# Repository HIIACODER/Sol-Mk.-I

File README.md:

# Sol Mk. I: A simple rocket flight controller
This project aims to create a flight controller for TVC, airbrakes, and fin control, that can charge and run off a 2 cell lipo battery and connect to it using an XT-30 connector. It uses a BMP581 barometer and an 
My goal with this project was to learn how to route properly and effectively on a PCB including how to manage decoupling caps and general power routing because that is what I struggle with. I also wanted a flight computer to use for my projects and test + learn C on.
I spent above 70 hours making this, and even more uncounted hours of research and thought, so I welcome any feedback.

This project should:
- help me develop a base to apply to future projects
- be a flight controller that I can reliably put in rockets

## PCB
Here is my PCB! This PCB was designed in KiCAD.

### General PCB design images

Schematic:

Top View (3d render):

Bottom View (3d render):

PCB Design:

First Layer: 

Second Layer:

Third Layer: 

Fourth Layer: 

Fifth Layer:

Sixth Layer:

### Layer Stackup
The board contains 6 layers. The purpose of all layers listed below.

| Layer | Description |
| :--- | :--- |
| 1 | Main routing layer |
| 2 | First ground layer for reference and signal separation |
| 3 | Second ground layer for reference and signal separation |
| 4 | Main Power Routing Layer |
| 5 | Third ground layer for reference and signal separation |
| 6 | Overflow routing layer |
### Flashing Instructions
Here are steps to flash a file to the MCU! 
1. Hold down the BOOTSEL button (the only button on the board) while plugging the board into your computer via USBC
2. The board will show up as a USB mass storage device
3. Compile your .uf2 binary file through external methods (C/C++ SDK, MicroPython, CircuitPython, etc)
4. Drag your compiled .uf2 file onto the drive. The board should automatically reboot and run the newly uploaded firmware!

## BOM

All SMD parts utilize 0402 passives, with 2 0603 for the MCU power to minimize board surface area. JLCPCB / LCSC part numbers are included below for reference.

| Item | Component / Description | Qty | Designators | Footprint | JLCPCB Part # | Unit Price (USD) |
| :--- | :--- | :---: | :--- | :--- | :--- | :---: |
| 1 | 1uF Capacitor | 3 | `C1, C10, C14` | `C_0402` | `C29266` | $0.0049 |
| 2 | 10uF Capacitor | 12 | `C11, C12, C13, C16, C17, C18, C2, C4, C5, C7, C8, C9` | `C_0402` | `C315248` | $0.0269 |
| 3 | 100nF Capacitor | 17 | `C15, C19, C20, C22, C24, C28, C29, C30, C31, C32, C33, C34, C35, C36, C40, C41, C42` | `C_0402` | `C1525` | $0.0029 |
| 4 | 10nF Capacitor | 1 | `C21` | `C_0402` | `C15195` | $0.0037 |
| 5 | 2.2uF Capacitor | 1 | `C23` | `C_0402` | `C444845` | $0.0094 |
| 6 | 4.7uF Capacitor | 2 | `C25, C26` | `C_0603` | `C19666` | $0.0150 |
| 7 | 47nF Capacitor | 1 | `C3` | `C_0402` | `C307434` | $0.0077 |
| 8 | 4.7uF Capacitor | 2 | `C37, C6` | `C_0402` | `C23733` | $0.0113 |
| 9 | 15pF Capacitor | 2 | `C38, C39` | `C_0402` | `C106997` | $0.0013 |
| 10 | TF-01A MicroSD Card Socket | 1 | `CARD1` | `TF-SMD_TF-01A` | `C91145` | $0.1931 |
| 11 | XT30UPB-M Power Connector | 1 | `CN1` | `CONN-TH_XT30UPB-M` | `C428721` | $0.2635 |
| 12 | USBLC6-2SC6 USB Protection IC | 1 | `D1` | `SOT-23-6_L2.9-W1.6-P0.95-LS2.8-BL` | `C7519` | $0.1559 |
| 13 | LED | 1 | `D2` | `LED0603-RD` | `C19273150` | $0.0114 |
| 14 | Green Signal LED | 1 | `D4` | `LED0603-GREEN` | `C22371297` | $0.0147 |
| 15 | 3-Pin Male Header | 5 | `H5, H6, H7, H8, H9` | `HDR-TH_3P-P2.54mm` | `C2937625` | $0.0200 |
| 16 | 1uH Inductor | 1 | `L1` | `APH252012C3R3MP01` | `C42455356` | $0.0365 |
| 17 | 3.3uH Inductor | 1 | `L2` | `B201610S3R3-101-T` | `C42411119` | $0.3377 |
| 18 | 5.1kΩ Resistor | 2 | `R1, R2` | `R0402` | `C25905` | $0.0014 |
| 19 | 10kΩ Resistor | 12 | `R6, R8, R9, R10, R11, R18, R19, R20, R21, R22, R23, R24` | `R0402` | `C25744` | $0.0010 |
| 20 | 10kΩ Thermistor | 1 | `TH1` | `R0402` | `C25744` | $0.0010 |
| 21 | 75kΩ Resistor | 1 | `R12` | `R0402` | `C2909383` | $0.0011 |
| 22 | 24kΩ Resistor | 1 | `R13` | `R0402` | `C25769` | $0.0012 |
| 23 | 100kΩ Resistor | 2 | `R14, R15` | `R0402` | `C25741` | $0.0011 |
| 24 | 105kΩ Resistor | 1 | `R16` | `R0402` | `C25742` | $0.0021 |
| 25 | 20kΩ Resistor | 1 | `R17` | `R0402` | `C25765` | $0.0011 |
| 26 | 1kΩ Resistor | 3 | `R7, R25, R26` | `R0402` | `C11702` | $0.0013 |
| 27 | 33Ω Resistor | 1 | `R27` | `R0402` | `C25105` | $0.0011 |
| 28 | 27Ω Resistor | 2 | `R28, R29` | `R0402` | `C2909343` | $0.0012 |
| 29 | 5.23kΩ Resistor | 1 | `R3` | `R0402` | `C2933105` | $0.0013 |
| 30 | 130Ω Resistor | 1 | `R30` | `R0402` | `C477610` | $0.0038 |
| 31 | 30.1kΩ Resistor | 1 | `R4` | `R0402` | `C29402` | $0.0012 |
| 32 | 383Ω Resistor | 1 | `R5` | `R0402` | `C49653730` | $0.0008 |
| 33 | TS-1088 Tactile Switch | 1 | `SW1` | `SW-SMD_L3.9-W3.0-P4.45` | `C720477` | $0.0516 |
| 34 | BQ25883RGER Battery Charger IC | 1 | `U1` | `VFQFPN-24_L4.0-W4.0-P0.50-BL-EP2.8` | `C544362` | $4.2249 |
| 35 | RP2354A Microcontroller | 1 | `U2` | `QFN-60_L7.0-W7.0-P0.40` | `C41378174` | $1.2562 |
| 36 | TPS82130SILR 3.3V Buck Converter | 2 | `U3, U4` | `USIP-8_L3.0-W2.8-P0.65` | `C473914` | $3.3384 |
| 37 | BMP581 Barometric Pressure Sensor | 1 | `U5` | `LGA-10_L2.0-W2.0-P0.50` | `C5362283` | $2.2539 |
| 38 | ICM-42688-P IMU Sensor | 1 | `U6` | `LGA-14_L3.0-W2.5-P0.50` | `C1850418` | $20.8264 |
| 39 | 12MHz Crystal | 1 | `U7` | `CRYSTAL-SMD_4P-L3.2-W2.5` | `C20625731` | $0.3817 |
| 40 | USB-C 16-Pin Connector | 1 | `USB1` | `USB-C-SMD_TYPE-C-16PIN-2MD-073` | `C2765186` | $0.0728 |

### Prices on JLCPCB:
NOTE: THESE PRICES DO NOT CONTAIN TAXES, AND ARE PRONE TO CHANGES
Parts Price (for 2): $96.3767

PCB (5x): $2.0 (if done without PCBA)

PCB (5x): $32.00

PCBA (2x): $194.03

Shipping on Global Standard Direct Line: $12.62

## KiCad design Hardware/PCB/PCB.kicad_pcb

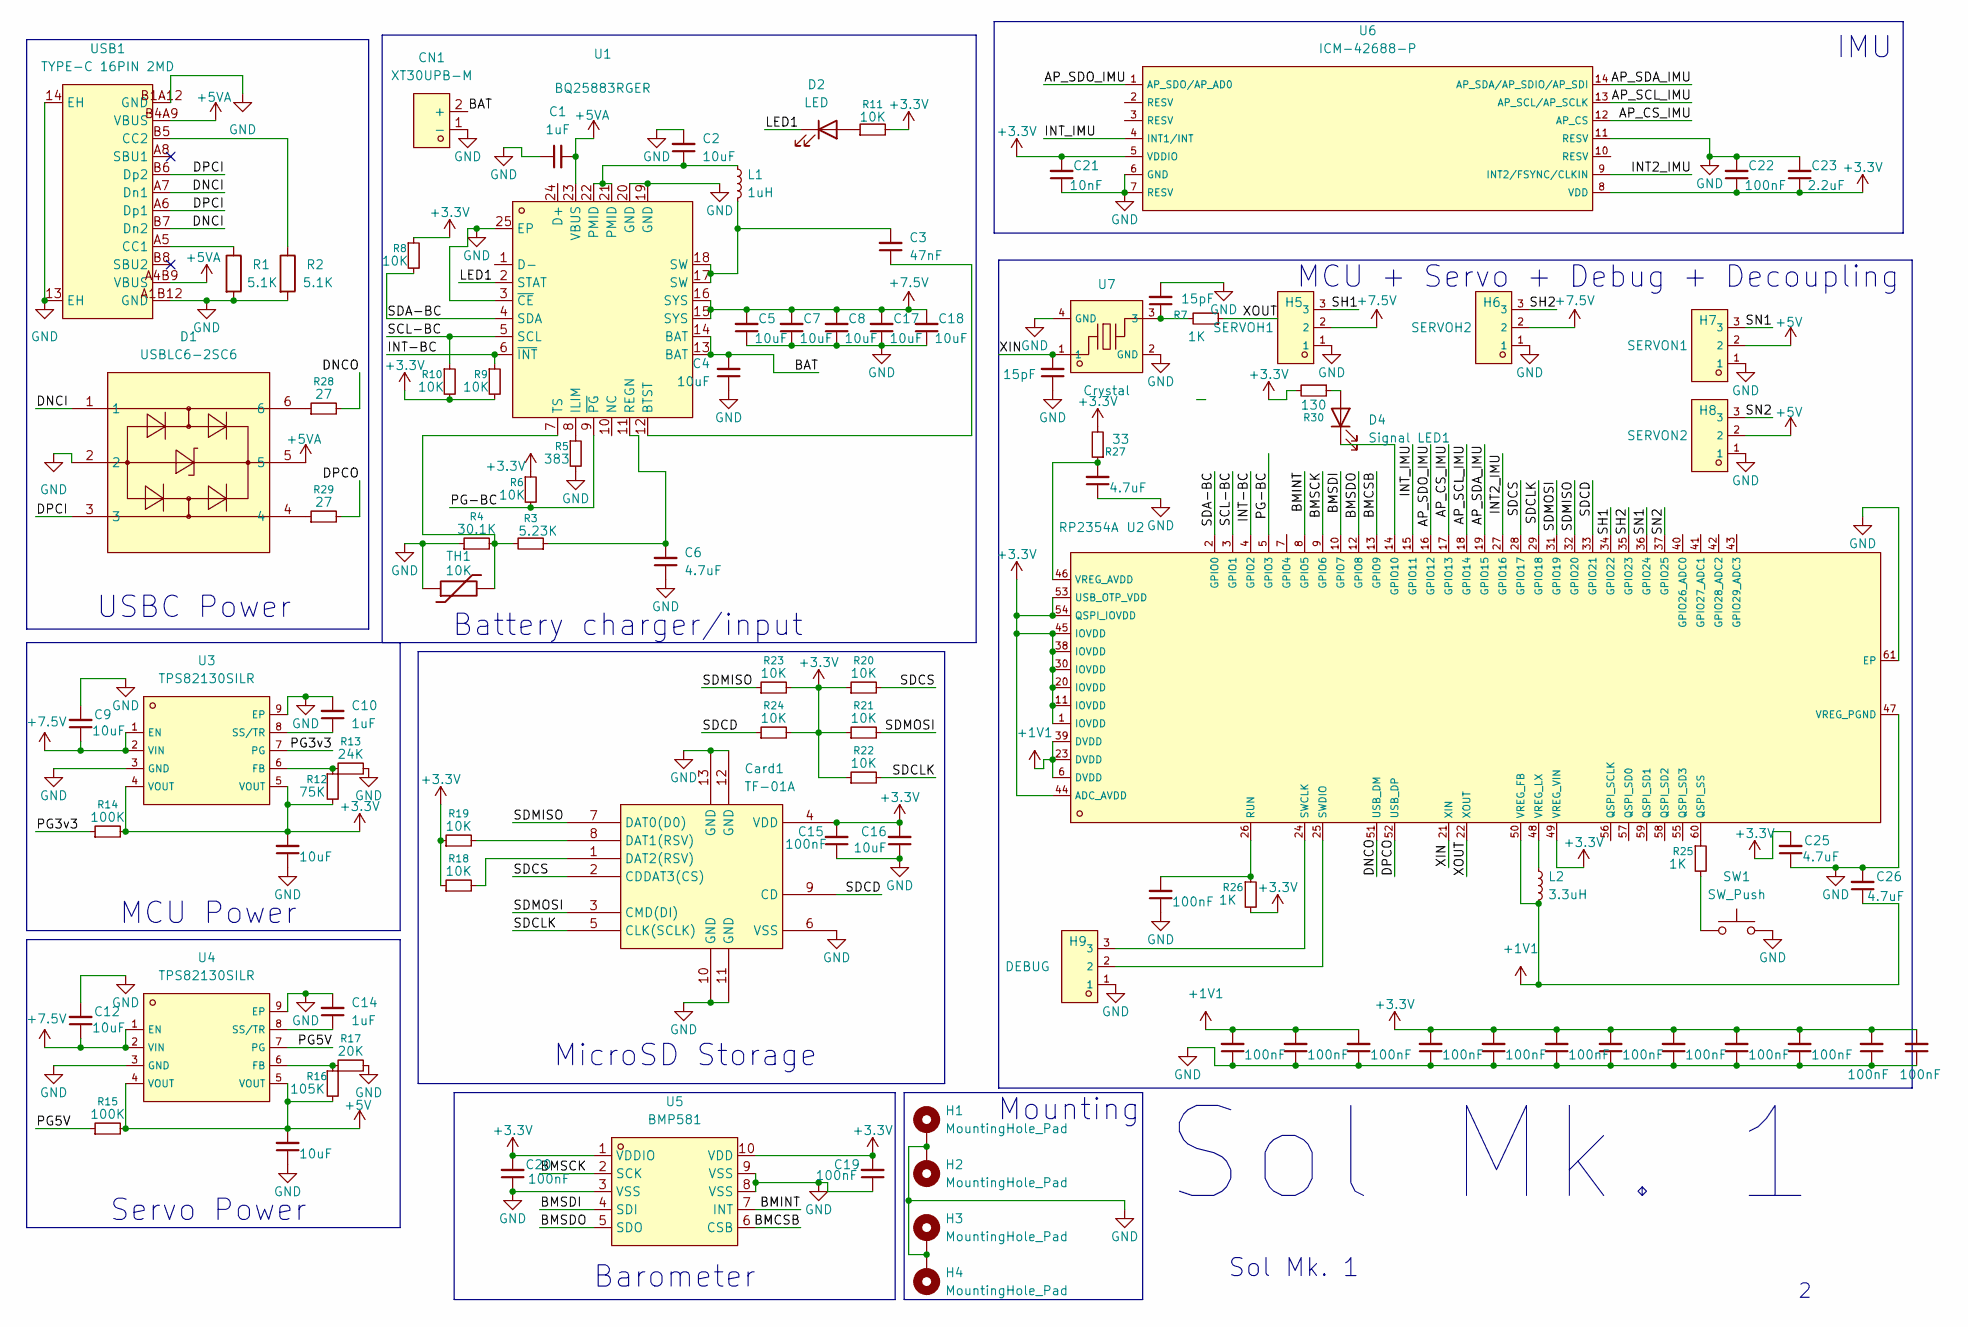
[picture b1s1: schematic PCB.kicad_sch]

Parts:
C1, C10, C14: 1uF; C_0402
C2, C4, C5, C7, C8, C9, C11, C12, C13, C16, C17, C18: 10uF; C_0402
C3: 47nF; C_0402
C6, C37: 4.7uF; C_0402
C15, C19, C20, C22, C24, C28, C29, C30, C31, C32, C33, C34, C35, C36, C40, C41, C42: 100nF; C_0402
C21: 10nF; C_0402
C23: 2.2uF; C_0402
C25, C26: 4.7uF; C_0603
C38, C39: 15pF; C_0402
CN1: XT30UPB-M; CONN-TH_XT30UPB-M; MPN XT30UPB-M; LCSC Part C428721
Card1: TF-01A; TF-SMD_TF-01A; MPN TF-01A; LCSC Part C91145
D1: USBLC6-2SC6; SOT-23-6_L2.9-W1.6-P0.95-LS2.8-BL; MPN USBLC6-2SC6; LCSC Part C7519
D2: LED; C19273150_LED0603-RD
D4: Signal LED1; C22371297_LED0603-RD_GREEN
H1, H2, H3, H4: MountingHole_Pad; MountingHole_2.5mm
H5: SERVOH1; C2937625_HDR-TH_3P-P2_54-V-M_PZ254V-11-03P; LCSC C2937625
H6: SERVOH2; C2937625_HDR-TH_3P-P2_54-V-M_PZ254V-11-03P; LCSC C2937625
H7: SERVON1; C2937625_HDR-TH_3P-P2_54-V-M_PZ254V-11-03P; LCSC C2937625
H8: SERVON2; C2937625_HDR-TH_3P-P2_54-V-M_PZ254V-11-03P; LCSC C2937625
H9: DEBUG; C2937625_HDR-TH_3P-P2_54-V-M_PZ254V-11-03P; LCSC C2937625
L1: 1uH; C42455356_IND-SMD_APH252012C3R3MP01
L2: 3.3uH; C42411119_IND-SMD_L2_0-W1_6_AOTA-B201610S3R3-101-T
R1, R2: 5.1K; R0402
R3: 5.23K; R0402
R4: 30.1K; R0402
R5: 383; R0402
R6, R8, R9, R10, R11, R18, R19, R20, R21, R22, R23, R24: 10K; R0402
R7, R25, R26: 1K; R0402
R12: 75K; R0402
R13: 24K; R0402
R14, R15: 100K; R0402
R16: 105K; R0402
R17: 20K; R0402
R27: 33; R0402
R28, R29: 27; R0402
R30: 130; R0402
SW1: SW_Push; C720477_SW-SMD_L3_9-W3_0-P4_45
TH1: 10K; R0402
U1: BQ25883RGER; VFQFPN-24_L4.0-W4.0-P0.50-BL-EP2.8; MPN BQ25883RGER; LCSC Part C544362
U2: RP2354A; C41378174_QFN-60_L7_0-W7_0-P0_40-TL-EP3_4; LCSC C41378174
U3, U4: TPS82130SILR; C473914_USIP-8_L3_0-W2_8-P0_65-TL-EP; LCSC C473914
U5: BMP581; LGA-10_L2.0-W2.0-P0.50-TL_BMP581; MPN BMP581; LCSC Part C5362283
U6: ICM-42688-P; C1850418_LGA-14_L3_0-W2_5-P0_50-TL; LCSC C1850418
U7: Crystal; C20625731_CRYSTAL-SMD_4P-L3_2-W2_5-BL; LCSC C20625731
USB1: TYPE-C 16PIN 2MD; USB-C-SMD_TYPE-C-16PIN-2MD-073; MPN TYPE-C 16PIN 2MD(073); LCSC Part C2765186

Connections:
+1V1: C26.1, C28.2, C29.2, C41.2, L2.2, U2.6 (DVDD), U2.23 (DVDD), U2.39 (DVDD), U2.50 (VREG_FB)
+3.3V: C11.2, C15.2, C16.2, C19.2, C20.2, C21.2, C22.1, C23.1, C25.2, C30.2, C31.2, C32.2, C33.2, C34.2, C35.2, C36.2, C40.2, C42.2, Card1.4 (VDD), R6.1, R8.1, R9.2, R10.2, R11.2, R12.2, R14.2, R18.1, R19.1, R20.1, R21.1, R22.1, R23.2, R24.2, R26.2, R27.2, R30.2, U2.1 (IOVDD), U2.11 (IOVDD), U2.20 (IOVDD), U2.30 (IOVDD), U2.38 (IOVDD), U2.44 (ADC_AVDD), U2.45 (IOVDD), U2.49 (VREG_VIN), U2.53 (USB_OTP_VDD), U2.54 (QSPI_IOVDD), U3.4 (VOUT), U3.5 (VOUT), U5.1 (VDDIO), U5.10 (VDD), U6.5 (VDDIO), U6.8 (VDD)
+5V: C13.2, H7.2, H8.2, R15.2, R16.2, U4.4 (VOUT), U4.5 (VOUT)
+5VA: C1.2, D1.5, U1.23 (VBUS), USB1.A4B9 (VBUS), USB1.B4A9 (VBUS)
+7.5V: C5.2, C7.2, C8.2, C9.1, C12.1, C17.2, C18.2, H5.2, H6.2, U1.15 (SYS), U1.16 (SYS), U3.1 (EN), U3.2 (VIN), U4.1 (EN), U4.2 (VIN)
/AP_CS_IMU: U2.17 (GPIO13), U6.12 (AP_CS)
/AP_SCL_IMU: U2.18 (GPIO14), U6.13 (AP_SCL/AP_SCLK)
/AP_SDA_IMU: U2.19 (GPIO15), U6.14 (AP_SDA/AP_SDIO/AP_SDI)
/AP_SDO_IMU: U2.16 (GPIO12), U6.1 (AP_SDO/AP_AD0)
/BAT: C4.2, CN1.2 (+), U1.13 (BAT), U1.14 (BAT)
/BMCSB: U2.13 (GPIO9), U5.6 (CSB)
/BMINT: U2.8 (GPIO5), U5.7 (INT)
/BMSCK: U2.9 (GPIO6), U5.2 (SCK)
/BMSDI: U2.10 (GPIO7), U5.4 (SDI)
/BMSDO: U2.12 (GPIO8), U5.5 (SDO)
/DNCI: D1.1, USB1.A7 (Dn1), USB1.B7 (Dn2)
/DNCO: R28.2, U2.51 (USB_DM)
/DPCI: D1.3, USB1.A6 (Dp1), USB1.B6 (Dp2)
/DPCO: R29.2, U2.52 (USB_DP)
/INT2_IMU: U2.27 (GPIO16), U6.9 (INT2/FSYNC/CLKIN)
/INT-BC: R9.1, U1.6 (~INT), U2.4 (GPIO2)
/INT_IMU: U2.15 (GPIO11), U6.4 (INT1/INT)
/LED1: D2.1 (K), U1.2 (STAT)
/PG3v3: R14.1, U3.7 (PG)
/PG5V: R15.1, U4.7 (PG)
/PG-BC: R6.2, U1.9 (~PG), U2.5 (GPIO3)
/SCL-BC: R10.1, U1.5 (SCL), U2.3 (GPIO1)
/SDA-BC: R8.2, U1.4 (SDA), U2.2 (GPIO0)
/SDCD: Card1.9 (CD), R24.1, U2.33 (GPIO21)
/SDCLK: Card1.5 (CLK(SCLK)), R22.2, U2.29 (GPIO18)
/SDCS: Card1.2 (CDDAT3(CS)), R20.2, U2.28 (GPIO17)
/SDMISO: Card1.7 (DAT0(D0)), R23.1, U2.32 (GPIO20)
/SDMOSI: Card1.3 (CMD(DI)), R21.2, U2.31 (GPIO19)
/SH1: H5.3, U2.34 (GPIO22)
/SH2: H6.3, U2.35 (GPIO23)
/SN1: H7.3, U2.36 (GPIO24)
/SN2: H8.3, U2.37 (GPIO25)
/XIN: C38.2, U2.21 (XIN), U7.1
/XOUT: R7.1, U2.22 (XOUT)
GND: C1.1, C2.2, C4.1, C5.1, C6.1, C7.1, C8.1, C9.2, C10.2, C11.1, C12.2, C13.1, C14.2, C15.1, C16.1, C17.1, C18.1, C19.1, C20.1, C21.1, C22.2, C23.2, C24.1, C25.1, C26.2, C28.1, C29.1, C30.1, C31.1, C32.1, C33.1, C34.1, C35.1, C36.1, C37.1, C38.1, C39.2, C40.1, C41.1, C42.1, CN1.1 (-), Card1.6 (VSS), Card1.10 (GND), Card1.11 (GND), Card1.12 (GND), Card1.13 (GND), D1.2, H1.1, H2.1, H3.1, H4.1, H5.1, H6.1, H7.1, H8.1, H9.1, R1.2, R2.2, R4.1, R5.2, R13.2, R17.2, SW1.2, TH1.1, U1.3 (~CE), U1.19 (GND), U1.20 (GND), U1.25 (EP), U2.47 (VREG_PGND), U2.61 (EP), U3.3 (GND), U3.9 (EP), U4.3 (GND), U4.9 (EP), U5.3 (VSS), U5.8 (VSS), U5.9 (VSS), U6.6 (GND), U6.7 (RESV), U6.11 (RESV), U7.2 (GND), U7.4 (GND), USB1.13 (EH), USB1.14 (EH), USB1.A1B12 (GND), USB1.B1A12 (GND)
unnamed: C2.1, L1.1, U1.21 (PMID), U1.22 (PMID)
unnamed: C3.2, L1.2, U1.17 (SW), U1.18 (SW)
unnamed: C39.1, R7.2, U7.3
unnamed: Card1.8 (DAT1(RSV)), R19.2
unnamed: Card1.1 (DAT2(RSV)), R18.2
unnamed: D1.4, R29.1
unnamed: D1.6, R28.1
unnamed: D2.2 (A), R11.1
unnamed: D4.2 (A), R30.1
unnamed: D4.1 (K), U2.14 (GPIO10)
unnamed: R25.2, SW1.1
unnamed: C3.1, U1.12 (BTST)
unnamed: R5.1, U1.8 (ILIM)
unnamed: C6.2, R3.1, U1.11 (REGN)
unnamed: R3.2, R4.2, TH1.2, U1.7 (TS)
unnamed: R25.1, U2.60 (QSPI_SS)
unnamed: C24.2, R26.1, U2.26 (RUN)
unnamed: H9.3, U2.24 (SWCLK)
unnamed: H9.2, U2.25 (SWDIO)
unnamed: C37.2, R27.1, U2.46 (VREG_AVDD)
unnamed: L2.1, U2.48 (VREG_LX)
unnamed: R12.1, R13.1, U3.6 (FB)
unnamed: C10.1, U3.8 (SS/TR)
unnamed: R16.1, R17.1, U4.6 (FB)
unnamed: C14.1, U4.8 (SS/TR)
unnamed: R1.1, USB1.A5 (CC1)
unnamed: R2.1, USB1.B5 (CC2)

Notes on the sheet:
Mounting
Servo Power
Sol Mk. 1
MCU + Servo + Debug + Decoupling
USBC Power
Barometer
Battery charger/input
IMU
MCU Power
MicroSD Storage

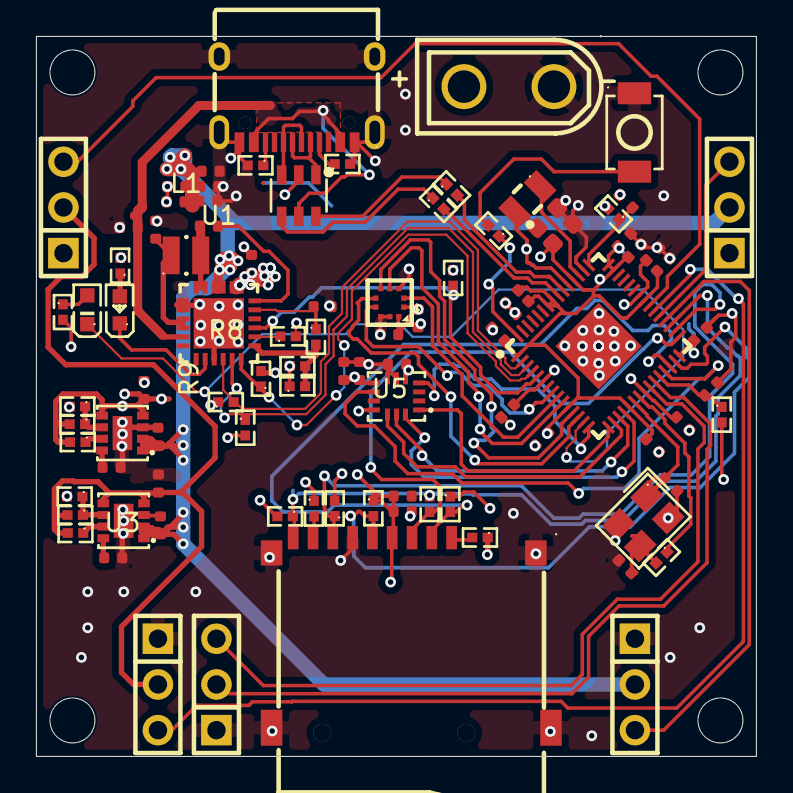
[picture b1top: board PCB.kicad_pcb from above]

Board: 6 copper layers, 40.0 x 40.0 mm, 97 parts (0 on the bottom side), 67 nets.

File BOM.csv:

Designator,Footprint,Quantity,Value,LCSC Part #
"C1, C10, C14",C_0402,3,1uF,
"C11, C12, C13, C16, C17, C18, C2, C4, C5, C7, C8, C9",C_0402,12,10uF,
"C15, C19, C20, C22, C24, C28, C29, C30, C31, C32, C33, C34, C35, C36, C40, C41, C42",C_0402,17,100nF,
C21,C_0402,1,10nF,
C23,C_0402,1,2.2uF,
"C25, C26",C_0603,2,4.7uF,
C3,C_0402,1,47nF,
"C37, C6",C_0402,2,4.7uF,
"C38, C39",C_0402,2,15pF,
CARD1,TF-SMD_TF-01A,1,TF-01A,C91145
CN1,CONN-TH_XT30UPB-M,1,XT30UPB-M,C428721
D1,SOT-23-6_L2.9-W1.6-P0.95-LS2.8-BL,1,USBLC6-2SC6,C7519
D2,C19273150_LED0603-RD,1,LED,C19273150
D4,C22371297_LED0603-RD_GREEN,1,Signal LED1,C22371297
H5,C2937625_HDR-TH_3P-P2_54-V-M_PZ254V-11-03P,1,SERVOH1,C2937625
H6,C2937625_HDR-TH_3P-P2_54-V-M_PZ254V-11-03P,1,SERVOH2,C2937625
H7,C2937625_HDR-TH_3P-P2_54-V-M_PZ254V-11-03P,1,SERVON1,C2937625
H8,C2937625_HDR-TH_3P-P2_54-V-M_PZ254V-11-03P,1,SERVON2,C2937625
H9,C2937625_HDR-TH_3P-P2_54-V-M_PZ254V-11-03P,1,DEBUG,C2937625
L1,C42455356_IND-SMD_APH252012C3R3MP01,1,1uH,C42455356
L2,C42411119_IND-SMD_L2_0-W1_6_AOTA-B201610S3R3-101-T,1,3.3uH,C42411119
"R1, R2",R0402,2,5.1K,C25104
"R10, R11, R18, R19, R20, R21, R22, R23, R24, R6, R8, R9, TH1",R0402,13,10K,C25104
R12,R0402,1,75K,C25104
R13,R0402,1,24K,C25104
"R14, R15",R0402,2,100K,C25104
R16,R0402,1,105K,C25104
R17,R0402,1,20K,C25104
"R25, R26, R7",R0402,3,1K,C25104
R27,R0402,1,33,C25104
"R28, R29",R0402,2,27,C25104
R3,R0402,1,5.23K,C25104
R30,R0402,1,130,C25104
R4,R0402,1,30.1K,C25104
R5,R0402,1,383,C25104
SW1,C720477_SW-SMD_L3_9-W3_0-P4_45,1,SW_Push,C720477
U1,VFQFPN-24_L4.0-W4.0-P0.50-BL-EP2.8,1,BQ25883RGER,C544362
U2,C41378174_QFN-60_L7_0-W7_0-P0_40-TL-EP3_4,1,RP2354A,C41378174
"U3, U4",C473914_USIP-8_L3_0-W2_8-P0_65-TL-EP,2,TPS82130SILR,C473914
U5,LGA-10_L2.0-W2.0-P0.50-TL_BMP581,1,BMP581,C5362283
U6,C1850418_LGA-14_L3_0-W2_5-P0_50-TL,1,ICM-42688-P,C1850418
U7,C20625731_CRYSTAL-SMD_4P-L3_2-W2_5-BL,1,Crystal,C20625731
USB1,USB-C-SMD_TYPE-C-16PIN-2MD-073,1,TYPE-C 16PIN 2MD,C2765186
